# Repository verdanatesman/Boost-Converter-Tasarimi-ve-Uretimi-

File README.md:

# Boost-Converter-Tasarimi-ve-Uretimi-
4.Sınıfta tasarım derdi için KiCad üzerinden Boost Converter devresi tasarımı ve üretim süreçleri raporlarda ve görsellerde görülebilir.

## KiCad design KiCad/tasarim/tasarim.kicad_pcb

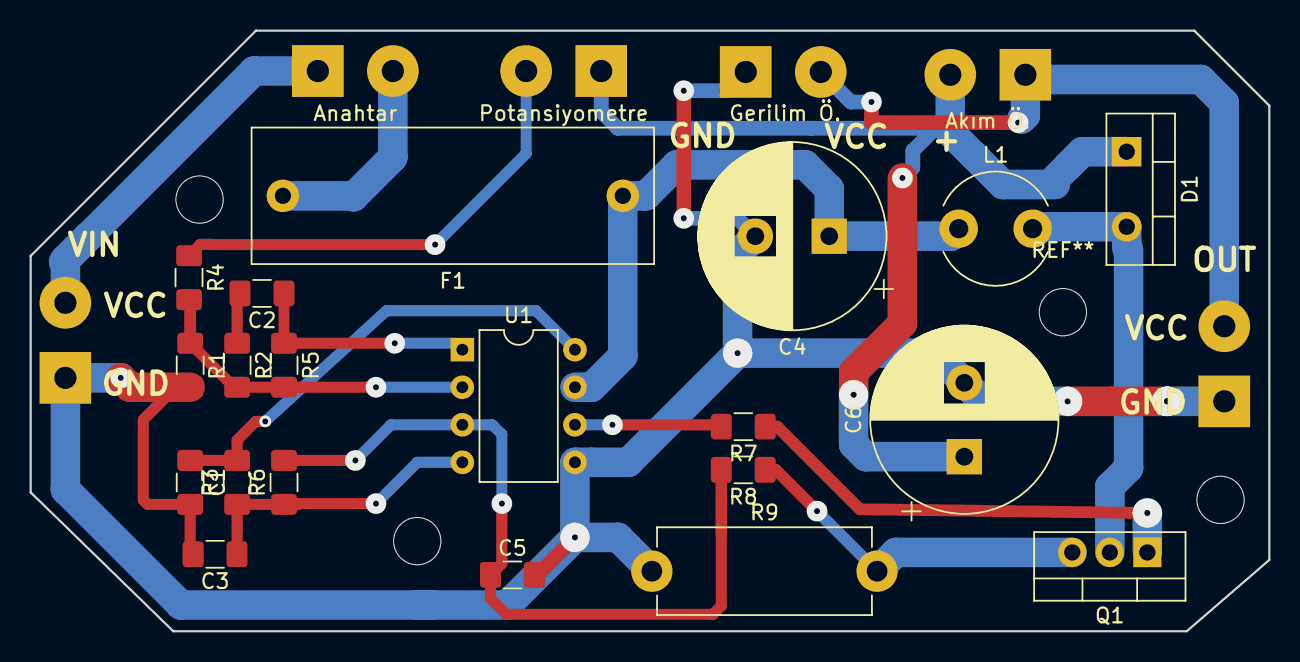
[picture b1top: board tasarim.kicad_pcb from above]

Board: 2 copper layers, 83.8 x 40.6 mm, 23 parts (0 on the bottom side), 15 nets.

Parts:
Akım Ö.: Akım Ö.; SolderWirePad_1x02_P5.08mm_Drill1.5mm
C1, C2: 10nF; C_1206_3216Metric_Pad1.42x1.75mm_HandSolder
C3, C5: 1nF; C_1206_3216Metric_Pad1.42x1.75mm_HandSolder
C4, C6: 1000uF; CP_Radial_D12.5mm_P5.00mm
D1: BYW29; TO-220-2_Vertical
F1: 5A Sigorta; C_Rect_L27.0mm_W9.0mm_P23.00mm
Gerilim Ö.: Gerilim Ö.; SolderWirePad_1x02_P5.08mm_Drill1.5mm
L1: 20uh; L_Radial_D7.5mm_P5.00mm_Fastron_07P
Potansiyometre: 100K POT; SolderWirePad_1x02_P5.08mm_Drill1.5mm
Q1: BUZ11; TO-220-3_Vertical
R1, R2, R3: 10K; R_1206_3216Metric_Pad1.42x1.75mm_HandSolder
R4: 27K; R_1206_3216Metric_Pad1.42x1.75mm_HandSolder
R5: 100K; R_1206_3216Metric_Pad1.42x1.75mm_HandSolder
R6: 15K; R_1206_3216Metric_Pad1.42x1.75mm_HandSolder
R7: 22r; R_1206_3216Metric_Pad1.42x1.75mm_HandSolder
R8: 1K; R_1206_3216Metric_Pad1.42x1.75mm_HandSolder
R9: 0.1R 5W; R_Axial_DIN0614_L14.3mm_D5.7mm_P15.24mm_Horizontal
U1: UC3843_DIP8; DIP-8_W7.62mm

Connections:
GNDREF: C1.2, C3.2, C4.2, C5.2, C6.2, Gerilim Ö..1, R1.2, R9.1, U1.5
unnamed: C1.1, R3.2, U1.8
unnamed: C2.1, R5.1, U1.1
unnamed: C2.2, R2.1
unnamed: C3.1, R3.1, R6.1, U1.4
unnamed: C4.1, F1.1, L1.1, U1.7
unnamed: C5.1, R6.2, R8.2, U1.3
unnamed: Akım Ö..2, C6.1, D1.1, Potansiyometre.1
unnamed: D1.2, L1.2, Q1.2
unnamed: Potansiyometre.2, R4.1
unnamed: Akım Ö..1, Gerilim Ö..2
unnamed: Q1.1, R7.1
unnamed: Q1.3, R8.1, R9.2
unnamed: R1.1, R2.2, R4.2, R5.2, U1.2
unnamed: R7.2, U1.6

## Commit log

2023-02-11 4.Sinif Kicad
